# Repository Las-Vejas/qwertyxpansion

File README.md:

# qwertyxpansion

This is a keyboard for the [Hackxpansion console](https://github.com/hackclub/hackxpansion). It features a qwerty keyboard, with 4 modifier keys and an LED. The switches are SPST.

I will be making the 3d case later on, as it's very hard to make correctly without the actual PCB.

## Images
|||
|---|---|
|||

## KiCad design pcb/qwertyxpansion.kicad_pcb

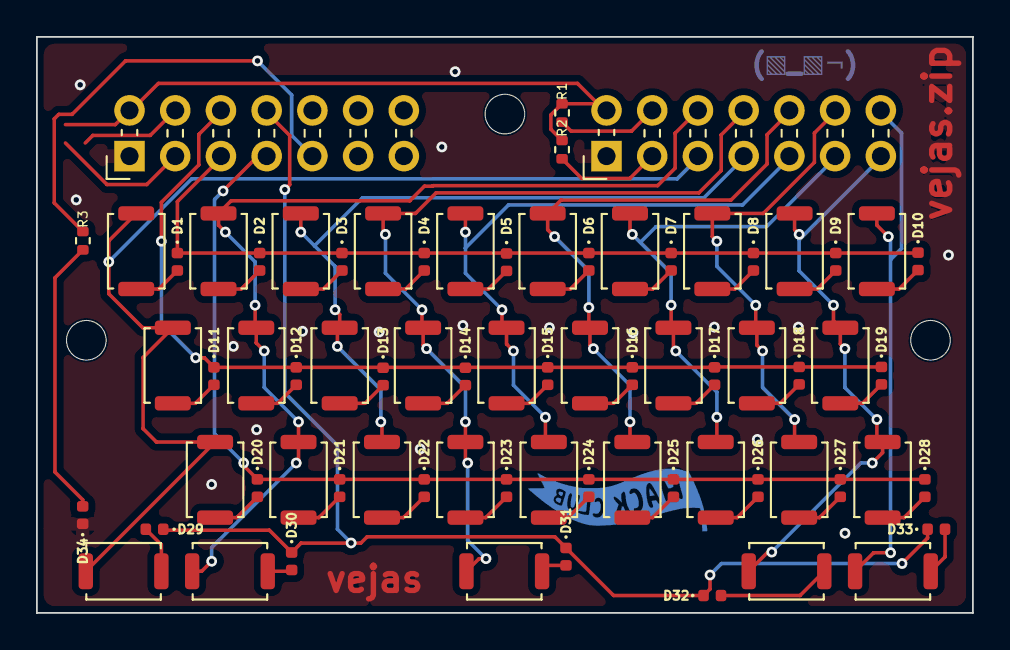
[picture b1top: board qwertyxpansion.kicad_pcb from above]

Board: 2 copper layers, 52.0 x 32.0 mm, 72 parts (0 on the bottom side), 53 nets.

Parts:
D1, D2, D3, D4, D5, D6, D7, D8, D9, D10, D11, D12, D13, D14, D15, D16, D17, D18, D19, D20, D21, D22, D23, D24, D25, D26, D27, D28, D29, D30, D31, D32, D33: D_Small; D_0402_1005Metric
D34: LED; D_0402_1005Metric
J1, J2: PinHeader_2x07_P2.54mm_Horizontal
R1: 75K; R_0402_1005Metric
R2: 1K; R_0402_1005Metric
R3: 300; R_0402_1005Metric
SW1: Q; SW_Push_SPST_NO_Alps_SKRK
SW2: W; SW_Push_SPST_NO_Alps_SKRK
SW3: E; SW_Push_SPST_NO_Alps_SKRK
SW4: R; SW_Push_SPST_NO_Alps_SKRK
SW5: T; SW_Push_SPST_NO_Alps_SKRK
SW6: Y; SW_Push_SPST_NO_Alps_SKRK
SW7: U; SW_Push_SPST_NO_Alps_SKRK
SW8: I; SW_Push_SPST_NO_Alps_SKRK
SW9: O; SW_Push_SPST_NO_Alps_SKRK
SW10: P; SW_Push_SPST_NO_Alps_SKRK
SW11: A; SW_Push_SPST_NO_Alps_SKRK
SW12: S; SW_Push_SPST_NO_Alps_SKRK
SW13: D; SW_Push_SPST_NO_Alps_SKRK
SW14: F; SW_Push_SPST_NO_Alps_SKRK
SW15: G; SW_Push_SPST_NO_Alps_SKRK
SW16: H; SW_Push_SPST_NO_Alps_SKRK
SW17: J; SW_Push_SPST_NO_Alps_SKRK
SW18: K; SW_Push_SPST_NO_Alps_SKRK
SW19: L; SW_Push_SPST_NO_Alps_SKRK
SW20: Z; SW_Push_SPST_NO_Alps_SKRK
SW21: X; SW_Push_SPST_NO_Alps_SKRK
SW22: C; SW_Push_SPST_NO_Alps_SKRK
SW23: V; SW_Push_SPST_NO_Alps_SKRK
SW24: B; SW_Push_SPST_NO_Alps_SKRK
SW25: N; SW_Push_SPST_NO_Alps_SKRK
SW26: M; SW_Push_SPST_NO_Alps_SKRK
SW27: ,; SW_Push_SPST_NO_Alps_SKRK
SW28: .; SW_Push_SPST_NO_Alps_SKRK
SW29, SW30, SW31, SW32, SW33: SW_Push_45deg; SW_Push_SPST_NO_Alps_SKRK

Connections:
+3V3: J1.2 (3V3), J2.2 (3V3), R1.1, R2.1
/COL1: J1.5 (GPIO0), SW1.1, SW11.1, SW20.1, SW29.1
/COL2: J1.6 (GPIO1), SW2.1, SW12.1, SW21.1, SW30.1
/COL3: J1.7 (GPI02), SW3.1, SW13.1, SW22.1
/COL4: J1.8 (GPIO3), SW4.1, SW14.1, SW23.1, SW31.1
/COL5: J1.9 (GPIO4), SW5.1, SW15.1, SW24.1
/COL6: J1.10 (GPIO5), SW6.1, SW16.1, SW25.1
/COL7: J1.11 (GPIO6), SW7.1, SW17.1, SW26.1
/COL8: J1.12 (GPIO7), SW8.1, SW18.1, SW27.1
/COL9: J1.13 (GPIO8), SW9.1, SW19.1, SW28.1, SW32.1
/COL10: J1.14 (GPIO9), SW10.1, SW33.1
/ROW1: D1.1 (K), D2.1 (K), D3.1 (K), D4.1 (K), D5.1 (K), D6.1 (K), D7.1 (K), D8.1 (K), D9.1 (K), D10.1 (K), J2.5 (GPIO0)
/ROW2: D11.1 (K), D12.1 (K), D13.1 (K), D14.1 (K), D15.1 (K), D16.1 (K), D17.1 (K), D18.1 (K), D19.1 (K), J2.6 (GPIO1)
/ROW3: D20.1 (K), D21.1 (K), D22.1 (K), D23.1 (K), D24.1 (K), D25.1 (K), D26.1 (K), D27.1 (K), D28.1 (K), J2.7 (GPI02)
/ROW4: D29.1 (K), D30.1 (K), D31.1 (K), D32.1 (K), D33.1 (K), J2.8 (GPIO3)
GND: D34.1 (K), J1.1 (GND), J2.1 (GND)
unnamed: D1.2 (A), SW1.2
unnamed: D2.2 (A), SW2.2
unnamed: D3.2 (A), SW3.2
unnamed: D4.2 (A), SW4.2
unnamed: D5.2 (A), SW5.2
unnamed: D6.2 (A), SW6.2
unnamed: D7.2 (A), SW7.2
unnamed: D8.2 (A), SW8.2
unnamed: D9.2 (A), SW9.2
unnamed: D10.2 (A), SW10.2
unnamed: D11.2 (A), SW11.2
unnamed: D12.2 (A), SW12.2
unnamed: D13.2 (A), SW13.2
unnamed: D14.2 (A), SW14.2
unnamed: D15.2 (A), SW15.2
unnamed: D16.2 (A), SW16.2
unnamed: D17.2 (A), SW17.2
unnamed: D18.2 (A), SW18.2
unnamed: D19.2 (A), SW19.2
unnamed: D20.2 (A), SW20.2
unnamed: D21.2 (A), SW21.2
unnamed: D22.2 (A), SW22.2
unnamed: D23.2 (A), SW23.2
unnamed: D24.2 (A), SW24.2
unnamed: D25.2 (A), SW25.2
unnamed: D26.2 (A), SW26.2
unnamed: D27.2 (A), SW27.2
unnamed: D28.2 (A), SW28.2
unnamed: D29.2 (A), SW29.2
unnamed: D30.2 (A), SW30.2
unnamed: D31.2 (A), SW31.2
unnamed: D32.2 (A), SW32.2
unnamed: D33.2 (A), SW33.2
unnamed: D34.2 (A), R3.2
unnamed: J1.3 (MD0), R2.2
unnamed: J1.4 (MD1), R1.2
unnamed: J2.9 (GPIO4), R3.1

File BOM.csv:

Reference,Price,Price,Value,LCSC Part #
"D1,D2,D3,D4,D5,D6,D7,D8,D9,D10,D11,D12,D13,D14,D15,D16,D17,D18,D19,D20,D21,D22,D23,D24,D25,D26,D27,D28,D29,D30,D31,D32,D33",1.44 $US,33,D_Small,C28646371
D34,0.69 $US,1,LED,C20608782
"J1,J2",0.00 $US,2,,
R1,0.19 $US,1,75K,C2909383
R2,0.15 $US,1,1K,C140197
R3,0.21 $US,1,300,C25102
"SW1,SW2,SW3,SW4,SW5,SW6,SW7,SW8,SW9,SW10,SW11,SW12,SW13,SW14,SW15,SW16,SW17,SW18,SW19,SW20,SW21,SW22,SW23,SW24,SW25,SW26,SW27,SW28,SW29,SW30,SW31,SW32,SW33",2.02 $US,33,SW_Push_45deg,C720477
PCB,4.00 $US,5,,
Stencil,3.07 $US,1,,
TOTAL,11.77 $US,,,

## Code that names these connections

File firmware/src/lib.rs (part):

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    },
};

/// ROW1..ROW4, on GPIO0..GPIO3 of the left connector (J2).
const ROWS: usize = 4;
/// COL1..COL10, on GPIO0..GPIO9 of the right connector (J1).
const COLS: usize = 10;

/// Time for a column to follow its row after the row is switched.
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
/// Driver for the qwertyxpansion keyboard, which spans two slots.
///
/// J1 (right) carries COL1..COL10 on GPIO0..GPIO9 and the ID resistors.
/// J2 (left) carries ROW1..ROW4 on GPIO0..GPIO3 and the LED on GPIO4.
pub struct QwertyDriver;

impl DriverMeta for QwertyDriver {
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        bus_allocator: &mut BusAllocator,
    ) -> Result<(), DriverError> {
        let cols = [
            right.gpio0.into(),
            right.gpio1.into(),
            right.gpio2.into(),
            right.gpio3.into(),
            right.gpio4.into(),
            right.gpio5.into(),
            right.gpio6.into(),
            right.gpio7.into(),
            right.gpio8.into(),
            right.gpio9.into(),
        ];
        let rows = [
            left.gpio0.into(),
            left.gpio1.into(),
            left.gpio2.into(),
            left.gpio3.into(),
        ];

        registry.register(
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            Box::new(KeyMatrix::new(rows, cols)) as Box<dyn Keyboard>,
        );

        // D34 is driven active-high from J2 GPIO4 through R3
        registry.register(
            slots.0,
            Self::ID,
            pin_led::<Generic>(left.gpio4.into(), false),
        );

        // we don't use any busses
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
